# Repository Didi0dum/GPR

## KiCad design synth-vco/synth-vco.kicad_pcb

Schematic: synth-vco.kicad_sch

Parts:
AR1: ADL5611ARKZ-R7; AMP_ADL5611ARKZ-R7; PARTREV B
AT1: PAT1220-C-3DB; ATTN_PAT1220-C-10DB-T5
C1, C11: 1n; C_0603_1608Metric_Pad1.08x0.95mm_HandSolder
C2: 1000p; C_0603_1608Metric_Pad1.08x0.95mm_HandSolder
C3, C10, C56, C57, C59, C61, C63: 100n; C_0603_1608Metric_Pad1.08x0.95mm_HandSolder
C4, C5, C12, C13, C14, C20, C22, C66, C68, C72: 100pF; C_0603_1608Metric_Pad1.08x0.95mm_HandSolder
C6: 160nF; C_1206_3216Metric_Pad1.33x1.80mm_HandSolder
C7: 5.6uF; C_1206_3216Metric_Pad1.33x1.80mm_HandSolder
C8, C50, C52, C53, C54: 10n; C_0603_1608Metric_Pad1.08x0.95mm_HandSolder
C9: 33nF; C_1206_3216Metric_Pad1.33x1.80mm_HandSolder
C15: 68pF; C_0603_1608Metric_Pad1.08x0.95mm_HandSolder
C16: 1.2nF; C_0603_1608Metric_Pad1.08x0.95mm_HandSolder
C17, C69: 1uF; C_0603_1608Metric_Pad1.08x0.95mm_HandSolder
C18: 100nF; C_0603_1608Metric_Pad1.08x0.95mm_HandSolder
C23, C31, C34, C36, C39, C42: 4.7u; C_0805_2012Metric_Pad1.18x1.45mm_HandSolder
C24, C29, C30, C32, C33, C35, C38, C41, C44, C70: 10u; C_0805_2012Metric_Pad1.18x1.45mm_HandSolder
C25, C27, C51, C55, C65: 10u; C_1206_3216Metric_Pad1.33x1.80mm_HandSolder
C26, C28: 22u; C_1206_3216Metric_Pad1.33x1.80mm_HandSolder
C37, C40, C43: 0.47u; C_0603_1608Metric_Pad1.08x0.95mm_HandSolder
C45: 470n; C_0603_1608Metric_Pad1.08x0.95mm_HandSolder
C46: 0.1u; C_0603_1608Metric_Pad1.08x0.95mm_HandSolder
C47: 2.2n; C_0603_1608Metric_Pad1.08x0.95mm_HandSolder
C48: 47p; C_0603_1608Metric_Pad1.08x0.95mm_HandSolder
C49: 4.7u; C_1206_3216Metric_Pad1.33x1.80mm_HandSolder
C58, C60, C62, C64: 10p; C_0603_1608Metric_Pad1.08x0.95mm_HandSolder
C67: 9pF; C_0603_1608Metric_Pad1.08x0.95mm_HandSolder
C71: 1.8pF; C_0603_1608Metric_Pad1.08x0.95mm_HandSolder
C73, C74: 2.2u; C_0805_2012Metric_Pad1.18x1.45mm_HandSolder
D1: MSS1P4-M3_89A; DIODE_MSS1P4-M3_89A
D3: WE-TVSP_DO; WE-TVSP_DO-214AC_UNIDIRECTIONAL
F1: MF-MSMF200/16X; FUSER_MF-MSMF200
FL1, FL2: BLM18EG331TZ1D; BEADC1608X65N; DigiKey_Part_Number 490-BLM18EG331TZ1DTR-ND
FL3, FL4: LFCN-900+; Filter_Mini-Circuits_FV1206
J1, J4: Conn_Coaxial; SMA_Samtec_SMA-J-P-H-ST-EM1_EdgeMount
J2: Screw_Terminal_01x02; TerminalBlock_CUI_TB007-508-02_1x02_P5.08mm_Horizontal
J3: 61202021621; J_Wurth_WR-BHD_61202021621; Working Voltage (V (AC)) 250
L1: 43nH; L_0603_1608Metric_Pad1.05x0.95mm_HandSolder
L2: 47.0 uH; L_Wurth_WE-LQS-4018; Part Number 74404042470
L3: 82uH; L_0805_2012Metric_Pad1.05x1.20mm_HandSolder
L5: 82nH; L_0603_1608Metric_Pad1.05x0.95mm_HandSolder
L6: 3.9nH; L_0603_1608Metric_Pad1.05x0.95mm_HandSolder
NT1: NetTie_2; NetTie-2_SMD_Pad0.5mm
R1: 5.1K; R_0603_1608Metric_Pad0.98x0.95mm_HandSolder
R2, R23: 2K; R_0603_1608Metric_Pad0.98x0.95mm_HandSolder
R3: 5.62; R_0603_1608Metric_Pad0.98x0.95mm_HandSolder
R4, R14, R15, R16, R17, R18, R19, R20, R21, R22, R30: 10K; R_0603_1608Metric_Pad0.98x0.95mm_HandSolder
R5: 1K; R_0603_1608Metric_Pad0.98x0.95mm_HandSolder
R6: 1.8K; R_0603_1608Metric_Pad0.98x0.95mm_HandSolder
R7: 33; R_0603_1608Metric_Pad0.98x0.95mm_HandSolder
R8, R38: 10; R_0603_1608Metric_Pad0.98x0.95mm_HandSolder
R9: 150; R_0603_1608Metric_Pad0.98x0.95mm_HandSolder
R10: 51; R_0603_1608Metric_Pad0.98x0.95mm_HandSolder
R11: 120; R_0603_1608Metric_Pad0.98x0.95mm_HandSolder
R12, R13: 75; R_0603_1608Metric_Pad0.98x0.95mm_HandSolder
R24, R25, R26: 49.9K; R_0603_1608Metric_Pad0.98x0.95mm_HandSolder
R27, R28: 32.4K; R_0603_1608Metric_Pad0.98x0.95mm_HandSolder; Tolerance 0.1%
R29: 32.4K; R_0603_1608Metric_Pad0.98x0.95mm_HandSolder
R31: 56k; R_0603_1608Metric_Pad0.98x0.95mm_HandSolder
R32: 226K; R_0603_1608Metric_Pad0.98x0.95mm_HandSolder
R33: 6.19K; R_0603_1608Metric_Pad0.98x0.95mm_HandSolder
R34: 1.15M; R_0603_1608Metric_Pad0.98x0.95mm_HandSolder
R35, R37: 60.4K; R_0603_1608Metric_Pad0.98x0.95mm_HandSolder
R36: 1.74M; R_0603_1608Metric_Pad0.98x0.95mm_HandSolder
R45, R46: 500K; R_0603_1608Metric_Pad0.98x0.95mm_HandSolder
U1: ADF4158; LFCSP-24-1EP_4x4mm_P0.5mm_EP2.5x2.5mm
U3: ADP-2-10+; CD636
U4: DAT-15R5A-SP+; MiniCircuits_DG983-2
U5: OPA192IDGKT; SOP65P490X110-8N
U6: TPSM53602RDAR; IC_TPSM53603RDAR; PARTREV A
U7, U8, U9, U10, U11, U12: LT3045IMSE_TRPBF; SOP65P490X110-13N; PARTREV D
U13: LT8570EMS8E_TRPBF; SOP65P490X110-9N; PARTREV A
U14, U15: LT3065EDDPBF; DFN-10_DD; MANUFACTURER_PART_NUMBER lt3065edd#pbf
U16: BT09E; SOT-89-3
Y1: FT3MN 26 MHz; TCXO_FT3MN_3.2x2.5mm
Y3: CVCO55CW-0500-1000; XTAL_CVCO55CW-0500-1000; DigiKey_Part_Number 744-1208-ND

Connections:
+3V3_PLL_A: C38.2, C59.1, C60.1, U1.6 (AVDD), U1.7 (AVDD), U1.8 (AVDD), U10.10 (OUTS), U10.11 (OUT), U10.12 (OUT)
+3V3_PLL_D: C41.2, C56.1, C57.1, C58.1, C61.1, C62.1, R4.2, R15.2, R16.2, R17.2, R18.2, R19.2, U1.18 (SDVDD), U1.19 (DVDD), U4.6 (VDD), U4.9 (VDD), U4.13 (VDD), U11.10 (OUTS), U11.11 (OUT), U11.12 (OUT)
+3V3_TCXO: C44.2, FL1.2, U12.10 (OUTS), U12.11 (OUT), U12.12 (OUT)
+5V_ADL5611: C15.1, C16.2, C17.2, C35.2, L1.2, U9.10 (OUTS), U9.11 (OUT), U9.12 (OUT)
+5V_BT09E: C32.2, C68.2, C69.2, C70.2, L5.2, U8.10 (OUTS), U8.11 (OUT), U8.12 (OUT)
+5V_VP: C24.2, C63.1, C64.1, U1.22 (VP), U7.10 (OUTS), U7.11 (OUT), U7.12 (OUT)
+6V_PRE: C26.2, C28.2, C29.2, C30.2, C33.2, C36.2, C39.2, C42.2, R22.2, U6.7 (VOUT), U6.8 (VOUT), U7.1 (IN), U7.2 (IN), U7.3 (IN), U7.4 (EN/UV), U7.7 (PGFB), U8.1 (IN), U8.2 (IN), U8.3 (IN), U8.4 (EN/UV), U8.7 (PGFB), U9.1 (IN), U9.2 (IN), U9.3 (IN), U9.4 (EN/UV), U9.7 (PGFB), U10.1 (IN), U10.2 (IN), U10.3 (IN), U10.4 (EN/UV), U10.7 (PGFB), U11.1 (IN), U11.2 (IN), U11.3 (IN), U11.4 (EN/UV), U11.7 (PGFB), U12.1 (IN), U12.2 (IN), U12.3 (IN), U12.4 (EN/UV), U12.7 (PGFB)
+12V_IN: C25.2, C27.2, C45.2, D3.1, F1.2, L2.1, R30.2, U6.1 (VIN), U6.2 (EN), U6.14 (VIN), U13.3 (VIN)
+12V_VCO: C50.2, C51.2, FL2.2, R34.1, U14.9 (OUT), U14.10 (OUT)
+18V_OPA: C18.1, C54.2, C55.2, R36.1, U5.7 (V+), U15.9 (OUT), U15.10 (OUT)
+20V_PRE: C65.2, C73.2, C74.2, R38.1, R45.1, R46.1, U14.1 (IN), U14.2 (IN), U14.3 (~SHDN), U15.1 (IN), U15.2 (IN), U15.3 (~SHDN)
/ATT_CLK: J3.15, U4.4 (CLK)
/ATT_DATA: J3.17, R20.1
/ATT_LE: J3.13, R21.2, U4.5 (LE)
/PLL_CE: J3.3, U1.13 (CE)
/PLL_LE: J3.9, U1.16 (LE)
/PLL_MUXOUT: C8.2, J3.11, R2.2, R4.1
/PLL_TXDATA: J3.1, U1.12 (TXDATA)
/SPI_CLK: J3.5, U1.14 (CLK)
/SPI_DATA: J3.7, U1.15 (DATA)
GND: AR1.2_4 (GND), AT1.3 (GND), C1.1, C3.1, C4.2, C6.2, C7.2, C8.1, C9.2, C10.1, C11.2, C15.2, C16.1, C17.1, C18.2, C23.1, C24.1, C25.1, C26.1, C27.1, C28.1, C29.1, C30.1, C31.1, C32.1, C33.1, C34.1, C35.1, C36.1, C37.1, C38.1, C39.1, C40.1, C41.1, C42.1, C43.1, C44.1, C45.1, C46.1, C47.1, C48.1, C49.1, C51.1, C52.1, C53.1, C55.1, C56.2, C57.2, C58.2, C59.2, C60.2, C61.2, C62.2, C63.2, C64.2, C65.1, C67.1, C68.1, C69.1, C70.1, C71.1, C73.1, C74.1, D3.2, FL3.2 (GND), FL3.4 (GND), FL4.2 (GND), FL4.4 (GND), J1.2 (Ext), J2.1, J3.2, J3.4, J3.6, J3.8, J3.10, J3.12, J3.14, J3.16, J3.18, J3.19, J3.20, J4.2 (Ext), NT1.2, R1.1, R5.2, R10.2, R12.1, R13.1, R14.1, R21.1, R24.2, R25.2, R26.2, R27.2, R28.2, R29.2, R31.1, R35.2, R37.2, U1.1 (CPGND), U1.2 (AGND), U1.3 (AGND), U1.10 (DGND), U1.11 (SDGND), U1.25 (AGND), U3.6 (GND), U4.10 (GND), U4.11 (GND), U4.12 (GND), U4.18 (GND), U4.21 (GND), U5.4 (V-), U6.3 (NC), U6.10 (NC), U6.11 (NC), U6.15 (PGND), U6.15_1 (PGND), U6.15_2 (PGND), U6.15_3 (PGND), U6.15_4 (PGND), U6.15_5 (PGND), U6.15_6 (PGND), U6.15_7 (PGND), U6.15_8 (PGND), U6.15_9 (PGND), U6.15_10 (PGND), U6.15_11 (PGND), U7.6 (ILIM), U7.9 (GND), U7.13 (EXP), U8.6 (ILIM), U8.9 (GND), U8.13 (EXP), U9.6 (ILIM), U9.9 (GND), U9.13 (EXP), U10.6 (ILIM), U10.9 (GND), U10.13 (EXP), U11.6 (ILIM), U11.9 (GND), U11.13 (EXP), U12.6 (ILIM), U12.9 (GND), U12.13 (EXP), U13.8 (SYNC), U13.9 (GND), U14.5 (IMAX), U14.7 (GND), U14.11 (GND), U15.5 (IMAX), U15.7 (GND), U15.11 (GND), U16.2 (GND), Y1.1 (GND), Y1.2 (GND), Y3.1 (GND), Y3.3 (GND), Y3.4 (GND), Y3.5 (GND), Y3.6 (GND), Y3.7 (GND), Y3.8 (GND), Y3.9 (GND), Y3.11 (GND), Y3.12 (GND), Y3.13 (GND), Y3.15 (GND), Y3.16 (GND)
unnamed: AR1.1 (RFIN), C13.2
unnamed: AR1.3 (RFOUT), C14.1, L1.1
unnamed: AT1.1 (IN), U3.4 (P2)
unnamed: AT1.2 (OUT), C20.1
unnamed: C5.2, R9.2, R10.1
unnamed: C7.1, R3.2
unnamed: C12.2, R8.1
unnamed: C13.1, R11.2, R13.2
unnamed: C47.2, R33.2
unnamed: C49.2, D1.1, R32.1, R38.2
unnamed: C71.2, C72.1, L6.2
unnamed: C14.2, FL3.1 (IN)
unnamed: FL3.3 (OUT), U3.1 (SUM)
unnamed: C72.2, FL4.1 (IN)
unnamed: FL4.3 (OUT), J4.1 (In)
unnamed: C20.2, J1.1 (In)
unnamed: F1.1, J2.2
unnamed: L3.2, R7.2
unnamed: R8.2, R9.1, R11.1, R12.2
unnamed: C6.1, R3.1, U1.24 (CP), U5.3 (+IN)
unnamed: R2.1, U1.17 (MUXOUT)
unnamed: C2.2, U1.9 (REFIN)
unnamed: C5.1, U1.5 (RFINA)
unnamed: C4.1, U1.4 (RFINB)
unnamed: R1.2, U1.23 (RSET)
unnamed: C22.2, U3.3 (P1)
unnamed: R18.1, U4.20 (C0.5)
unnamed: R17.1, U4.19 (C1)
unnamed: R16.1, U4.17 (C2)
unnamed: R15.1, U4.16 (C4)
unnamed: R19.1, U4.15 (C8)
unnamed: R20.2, U4.3 (DATA)
unnamed: R14.2, U4.1 (N/C)
unnamed: C22.1, U4.2 (RF_in)
unnamed: C66.1, U4.14 (RFout)
unnamed: R5.1, R6.1, U5.2 (-IN)
unnamed: R6.2, R7.1, U5.6 (OUT)
unnamed: NT1.1, R23.1, U6.12 (AGND)
unnamed: R22.1, R23.2, U6.9 (FB)
unnamed: C23.2, R24.1, U7.8 (SET)
unnamed: C31.2, R25.1, U8.8 (SET)
unnamed: C34.2, R26.1, U9.8 (SET)
unnamed: C37.2, R27.1, U10.8 (SET)
unnamed: C40.2, R28.1, U11.8 (SET)
unnamed: C43.2, R29.1, U12.8 (SET)
unnamed: R32.2, U13.1 (FBX)
unnamed: R31.2, U13.6 (RT)
unnamed: C46.2, U13.7 (SS)
unnamed: D1.2, L2.2, U13.4 (SW)
unnamed: C48.2, R33.1, U13.2 (VC)
unnamed: R30.1, U13.5 (~SHDN)
unnamed: C50.1, R34.2, R35.1, U14.8 (ADJ)
unnamed: R45.2, U14.4 (PWRGD)
unnamed: C52.2, U14.6 (REF/BYP)
unnamed: C54.1, R36.2, R37.1, U15.8 (ADJ)
unnamed: R46.2, U15.4 (PWRGD)
unnamed: C53.2, U15.6 (REF/BYP)
unnamed: C66.2, C67.2, U16.1 (RF_in)
unnamed: L5.1, L6.1, U16.3 (RF_out)
unnamed: C2.1, Y1.3 (OUT)
unnamed: C1.2, C3.2, FL1.1, Y1.4 (VDD)
unnamed: C12.1, Y3.10 (RF-OUT)
unnamed: C10.2, C11.1, FL2.1, Y3.14 (VCC)
unnamed: C9.1, L3.1, Y3.2 (VT)

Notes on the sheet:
5V Lines
3V3 Lines
12V Line
Boost to 20V
18V Line

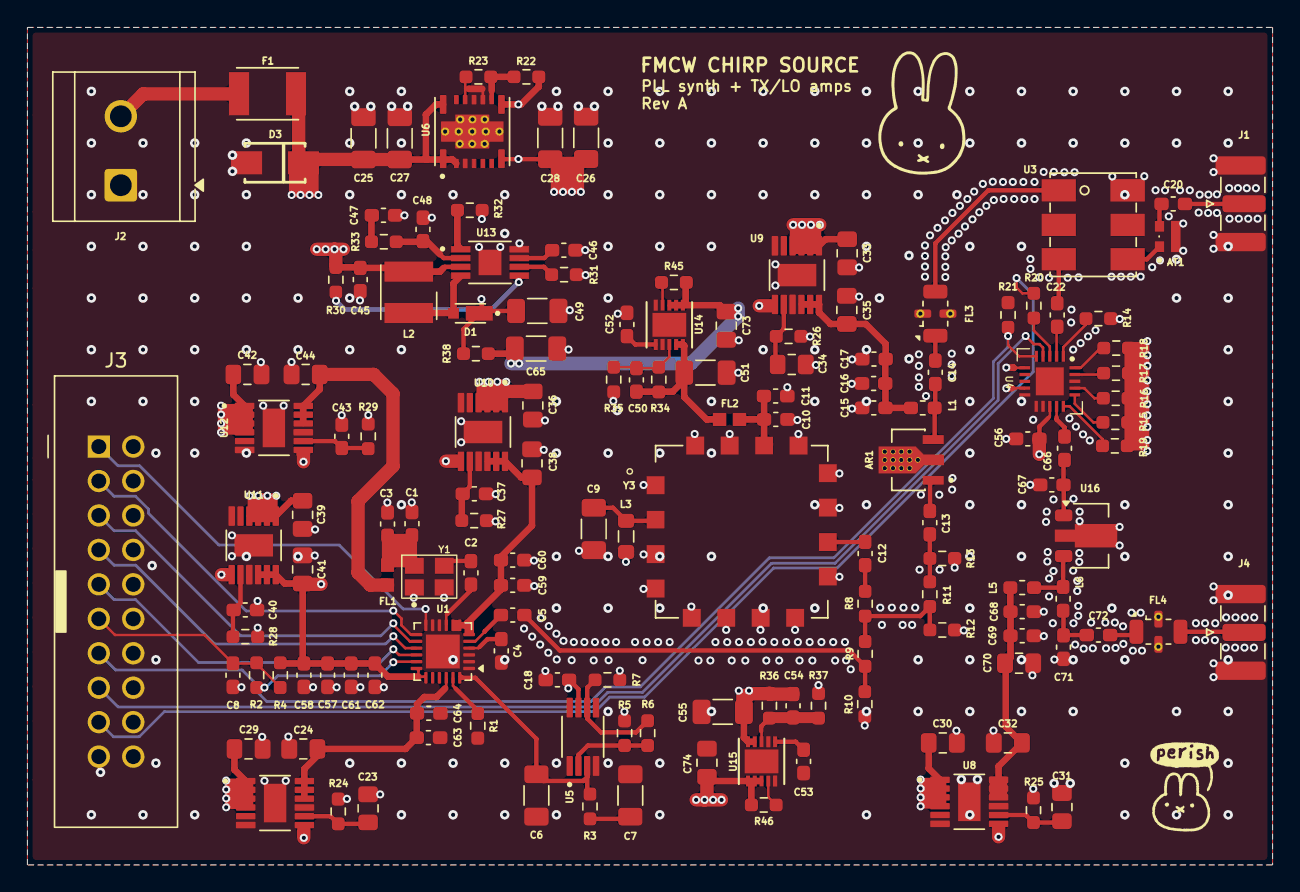
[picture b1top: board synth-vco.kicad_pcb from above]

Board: 4 copper layers, 91.8 x 61.8 mm, 148 parts (0 on the bottom side), 85 nets.
